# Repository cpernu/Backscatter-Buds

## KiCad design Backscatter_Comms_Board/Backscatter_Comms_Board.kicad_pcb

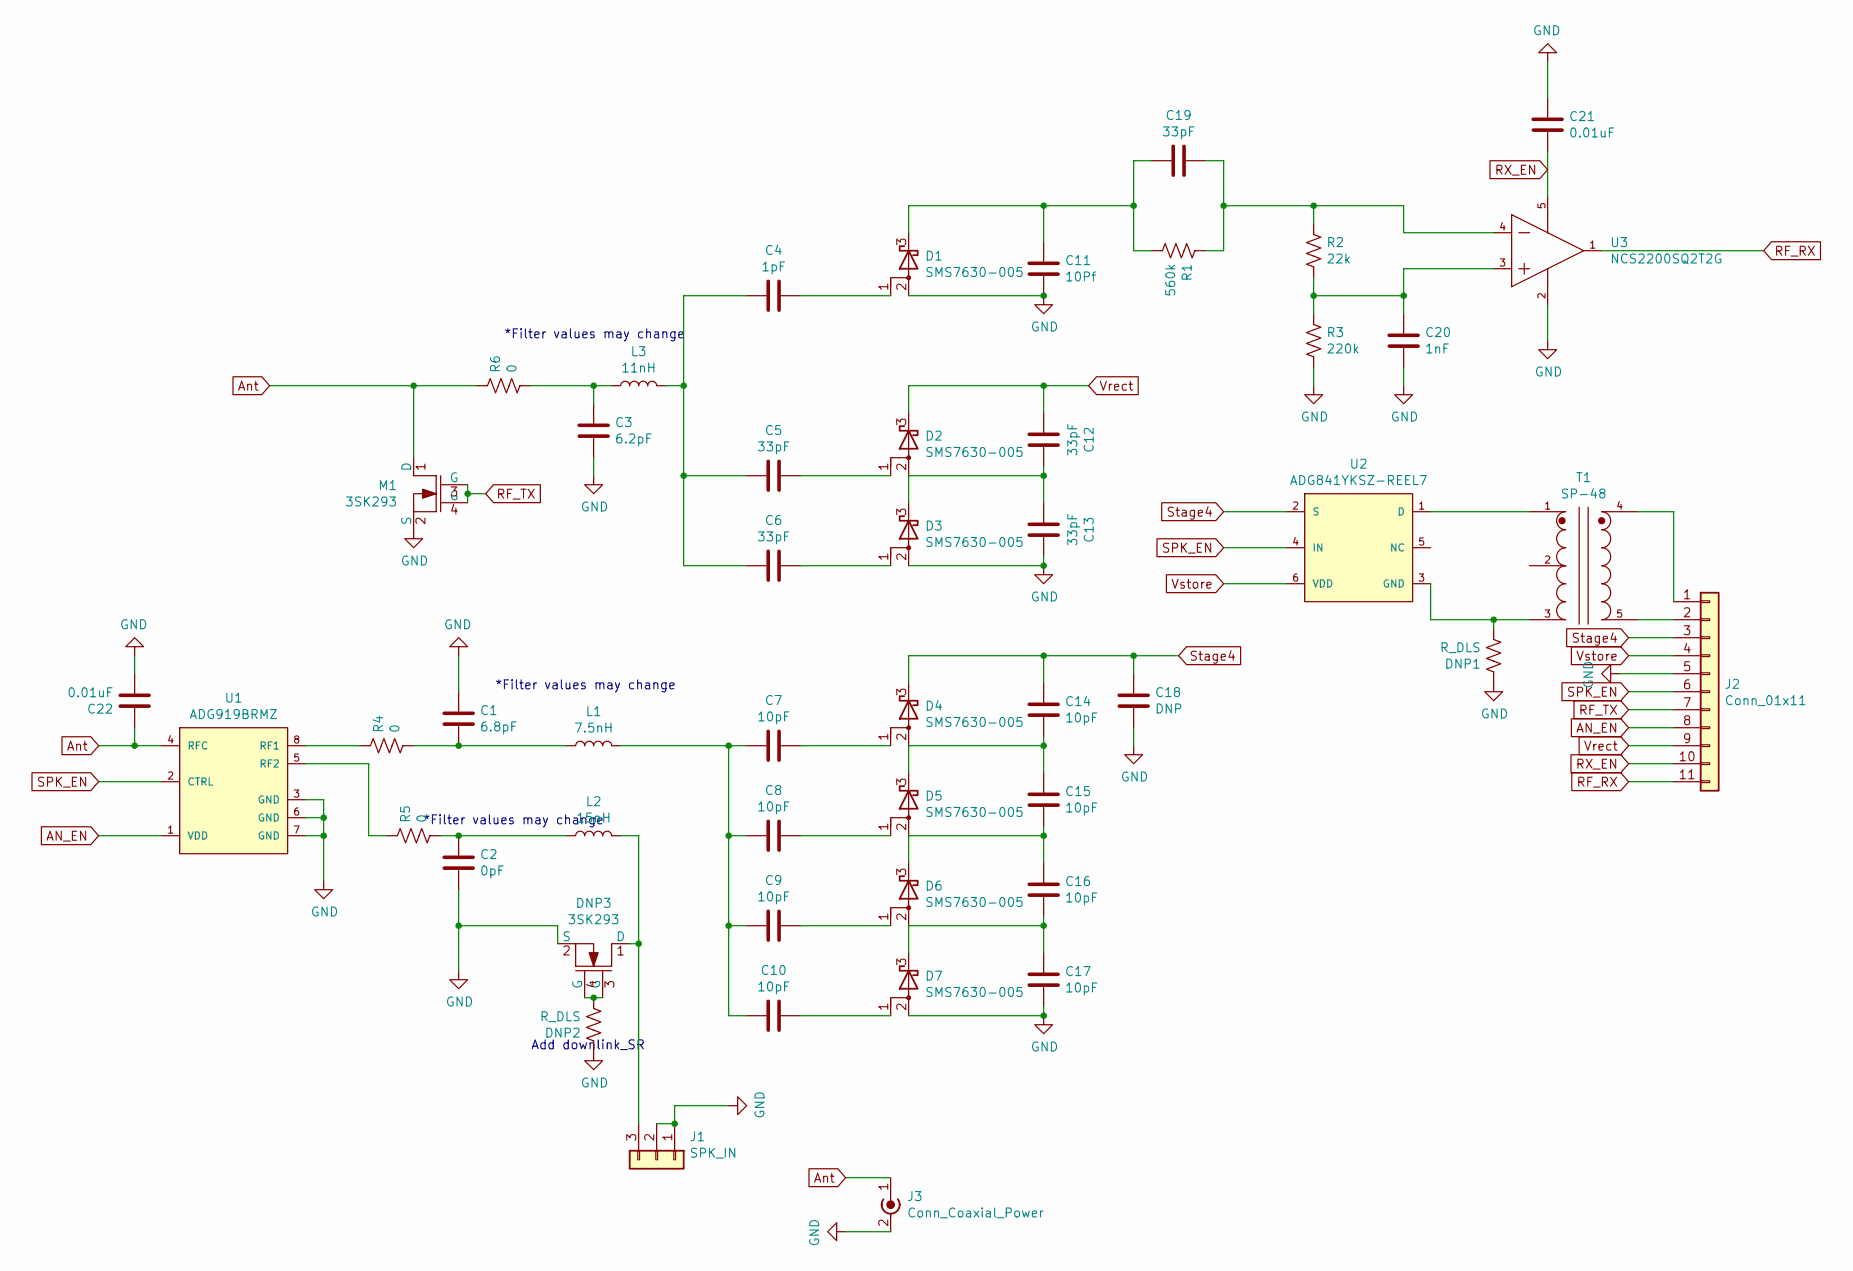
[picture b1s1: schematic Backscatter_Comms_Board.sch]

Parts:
C1: 6.8pF; C_0402_1005Metric_Pad0.74x0.62mm_HandSolder
C2: 0pF; C_0402_1005Metric_Pad0.74x0.62mm_HandSolder
C3: 6.2pF; C_0402_1005Metric_Pad0.74x0.62mm_HandSolder
C4: 1pF; C_0402_1005Metric_Pad0.74x0.62mm_HandSolder
C5, C6, C12, C13, C19: 33pF; C_0402_1005Metric_Pad0.74x0.62mm_HandSolder
C7, C8, C9, C10, C14, C15, C16, C17: 10pF; C_0402_1005Metric_Pad0.74x0.62mm_HandSolder
C11: 10Pf; C_0402_1005Metric_Pad0.74x0.62mm_HandSolder
C18: DNP; C_0402_1005Metric_Pad0.74x0.62mm_HandSolder
C20: 1nF; C_0402_1005Metric_Pad0.74x0.62mm_HandSolder
C21, C22: 0.01uF; C_0402_1005Metric_Pad0.74x0.62mm_HandSolder
D1, D2, D3, D4, D5, D6, D7: SMS7630-005; SOT95P237X112-3N
DNP1, DNP2: R_DLS; R_0402_1005Metric_Pad0.72x0.64mm_HandSolder
DNP3: 3SK293
J1: SPK_IN; Multi-purpose_mic
J2: Conn_01x11; PinHeader_1x11_P2.54mm_Vertical
J3: Conn_Coaxial_Power; MMCX_Molex_73415-0961_Horizontal_0.8mm-PCB
L1: 7.5nH; L_0402_1005Metric
L2: 15nH; L_0402_1005Metric
L3: 11nH; L_0402_1005Metric
M1: 3SK293
R1: 560k; R_0402_1005Metric_Pad0.72x0.64mm_HandSolder
R2: 22k; R_0402_1005Metric_Pad0.72x0.64mm_HandSolder
R3: 220k; R_0402_1005Metric_Pad0.72x0.64mm_HandSolder
R4, R5, R6: 0; R_0402_1005Metric_Pad0.72x0.64mm_HandSolder
T1: SP-48; XFMR_SP-48
U1: ADG919BRMZ; Analog_Devices-ADG919BRMZ-Level_C; Supply Voltage Single (+1.65V to +2.75V)
U2: ADG841YKSZ-REEL7; Analog_Devices-ADG841YKSZ-REEL7-Level_C
U3: NCS2200SQ2T2G; On_Semiconductor-NCS2200SQ2T2G-Manufacturer_Recommended

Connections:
AN_EN: J2.8, U1.1 (VDD)
Ant: C22.1, J3.1 (In), M1.1 (D), R6.1, U1.4 (RFC)
GND: C1.1, C2.2, C3.2, C11.2, C13.2, C17.2, C18.2, C20.2, C21.1, C22.2, D1.2 (A), D3.2 (A), D7.2 (A), DNP1.1, DNP2.1, DNP3.2 (S), J1.1, J1.2, J2.5, J3.2 (Ext), M1.2 (S), R3.2, U1.3 (GND), U1.6 (GND), U1.7 (GND), U3.2 (VEE)
unnamed: C1.2, L1.1, R4.2
unnamed: C2.1, L2.1, R5.2
unnamed: C3.1, L3.1, R6.2
unnamed: C4.1, C5.1, C6.1, L3.2
unnamed: C4.2, D1.1 (A)
unnamed: C5.2, D2.1 (A)
unnamed: C6.2, D3.1 (A)
unnamed: C7.2, D4.1 (A)
unnamed: C8.2, D5.1 (A)
unnamed: C9.2, D6.1 (A)
unnamed: C7.1, C8.1, C9.1, C10.1, L1.2
unnamed: C10.2, D7.1 (A)
unnamed: C11.1, C19.2, D1.3 (K), R1.2
unnamed: C12.2, C13.1, D2.2 (A), D3.3 (K)
unnamed: C14.2, C15.1, D4.2 (A), D5.3 (K)
unnamed: C15.2, C16.1, D5.2 (A), D6.3 (K)
unnamed: C16.2, C17.1, D6.2 (A), D7.3 (K)
unnamed: C19.1, R1.1, R2.1, U3.4 (IN-)
unnamed: C20.1, R2.2, R3.1, U3.3 (IN+)
unnamed: DNP1.2, T1.3, U2.3 (GND)
unnamed: DNP2.2, DNP3.3 (G), DNP3.4 (G)
unnamed: DNP3.1 (D), J1.3, L2.2
unnamed: J2.1, T1.4
unnamed: J2.2, T1.5
unnamed: R4.1, U1.8 (RF1)
unnamed: R5.1, U1.5 (RF2)
unnamed: T1.1, U2.1 (D)
RF_RX: J2.11, U3.1 (OUT)
RF_TX: J2.7, M1.3 (G), M1.4 (G)
RX_EN: C21.2, J2.10, U3.5 (VCC)
SPK_EN: J2.6, U1.2 (CTRL), U2.4 (IN)
Stage4: C14.1, C18.1, D4.3 (K), J2.3, U2.2 (S)
Vrect: C12.1, D2.3 (K), J2.9
Vstore: J2.4, U2.6 (VDD)

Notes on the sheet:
*Filter values may change
Add downlink_SR

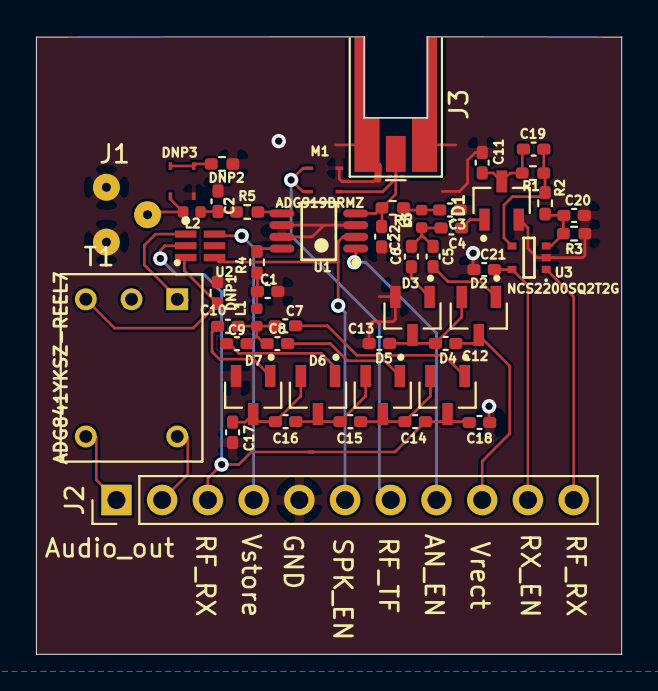
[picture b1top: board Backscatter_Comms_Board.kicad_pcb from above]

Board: 2 copper layers, 32.5 x 34.3 mm, 49 parts (0 on the bottom side), 37 nets.

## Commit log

2021-07-12 Initial-Commit
2021-07-13 Meeting notes
2021-07-13 I hope i didnt break the schematic
2021-07-13 rolled back cause the PCB broke
2021-07-13 test update
2021-07-15 Too big version
2021-07-19 V2 incorporating first round review
2021-07-21 Redid Board layou
    Even smaller rf path and other fun things
2021-07-23 Routed Main components
    All components routed except the i/o pins
2021-07-23 Final?
    This will be the final of today unless we decide to do a design review
2021-07-26 Small fixes final
    fixed nmos enclosure(again) and added better text
2021-07-26 This is the real one
2021-07-26 Almost complete :)
2021-07-27 Final v1 backscatter board
    Sending to oshpark right after I push!
2021-07-27 Post mini design review edits
    actually ordering this now!
2021-11-11 Pre-fabrication beta board
    I hope everything looks okay!
2021-11-11 trying to make commit workj >:(
